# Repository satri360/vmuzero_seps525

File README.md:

# vmuzero_seps525
Dreamcast VMU powered by Raspberry Pi Zero Project

Check [Build Instructions](https://sudomod.com/forum/viewtopic.php?f=62&t=6917) in sudomod.

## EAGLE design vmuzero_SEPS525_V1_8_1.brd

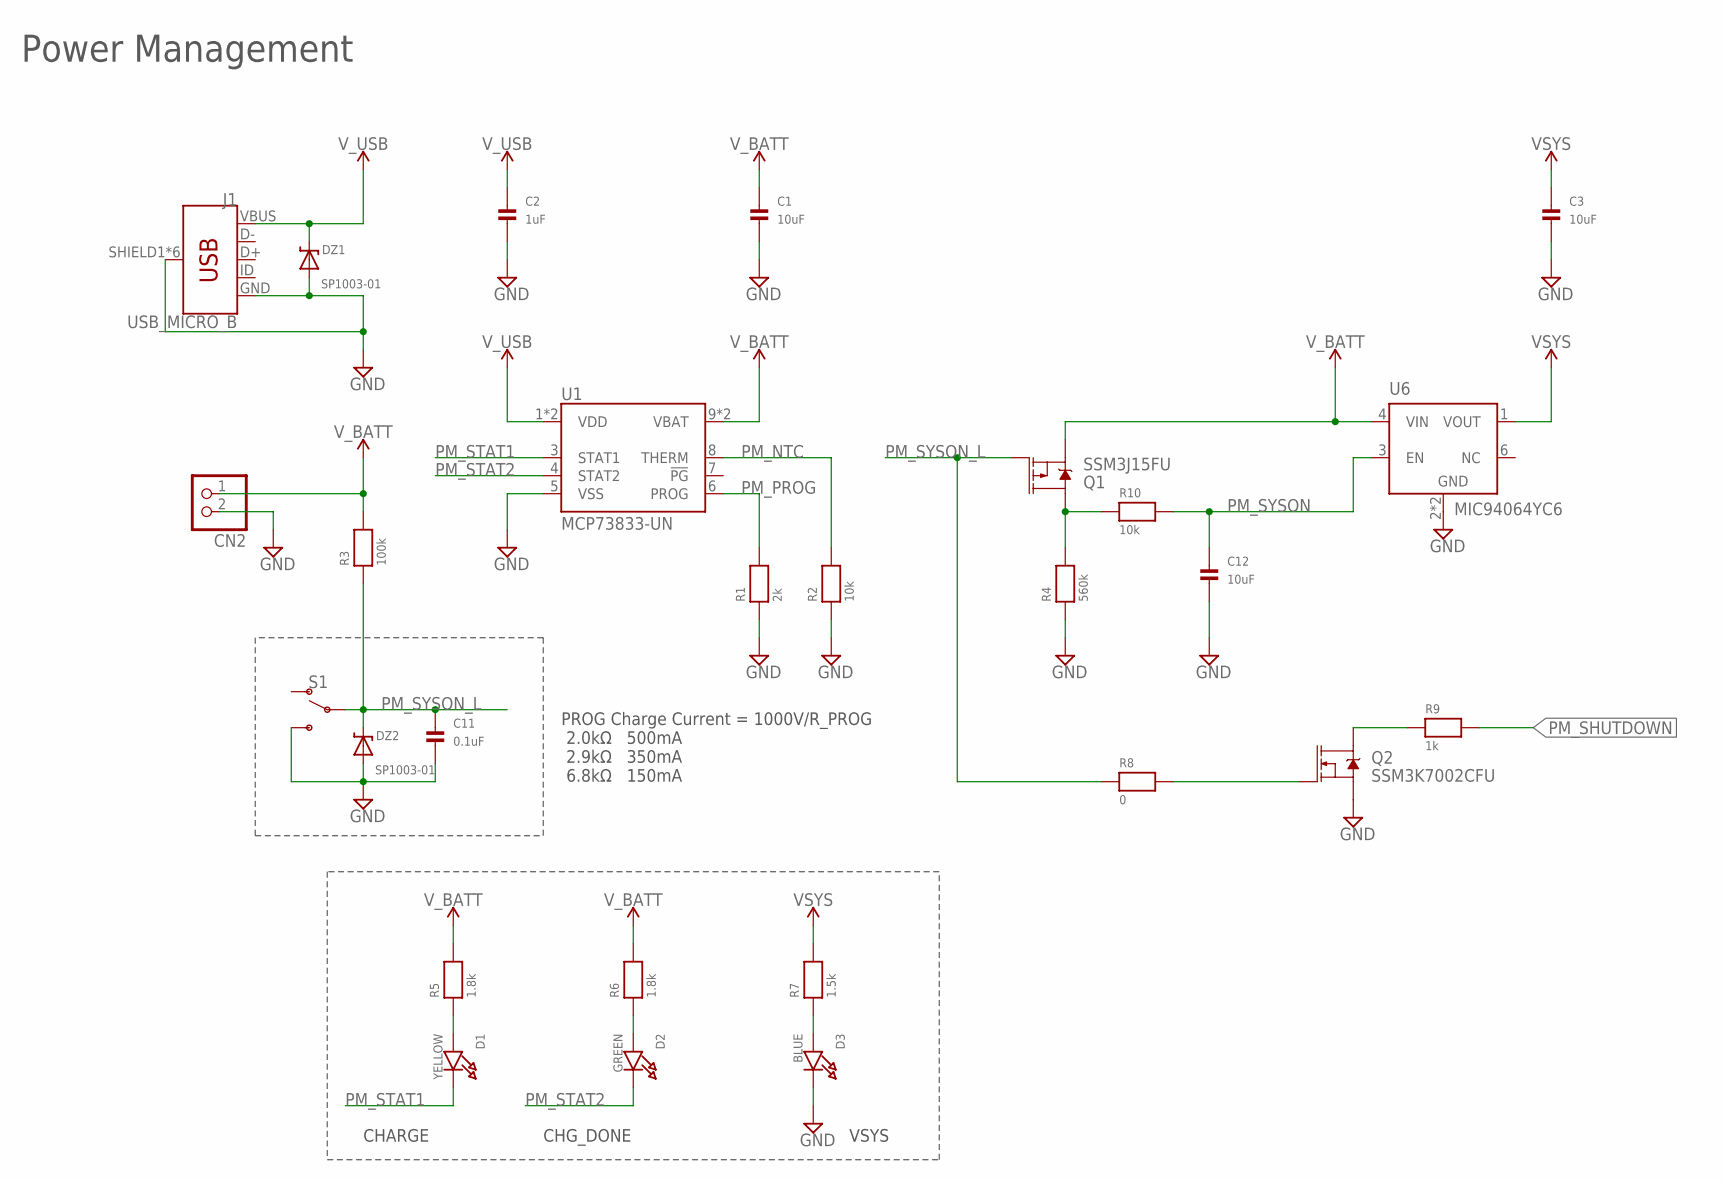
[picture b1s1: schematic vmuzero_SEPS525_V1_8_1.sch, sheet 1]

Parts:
C1, C3, C12: 10uF; _0805MP
C2: 1uF; _0805MP
C11: 0.1uF; _0805MP
CN2: JST_2PIN; S2B-PH-K-S
D1: YELLOW; CHIPLED_0805_NOOUTLINE
D2: GREEN; CHIPLED_0805_NOOUTLINE
D3: BLUE; CHIPLED_0805_NOOUTLINE
DZ1, DZ2: SP1003-01; DIODE_SOD723
J1: USB_MICRO_B; USB-MICROB_10118192
Q1: SSM3J15FU; SOT323
Q2: SSM3K7002CFU; SOT323
R1: 2k; _0805MP
R2, R10: 10k; _0805MP
R3: 100k; _0805MP
R4: 560k; _0805MP
R5, R6: 1.8k; _0805MP
R7: 1.5k; _0805MP
R8: 0; _0805MP
R9: 1k; _0805MP
S1: SWITCH-SPDT; SPDT_JS102011SAQN
U1: MCP73833-UN; 10L_MSOP
U6: MIC94064YC6; SC70-6L

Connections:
GND: C1.2, C2.2, C3.2, C11.2, C12.2, CN2.2 (1), D3.C, DZ1.A, DZ2.A, J1.GND, J1.SHIELD1 (SHIELD), J1.SHIELD2 (SHIELD), J1.SHIELD3 (SHIELD), J1.SHIELD4 (SHIELD), J1.SHIELD5 (SHIELD), J1.SHIELD6 (SHIELD), Q2.2 (S), R1.1, R2.1, R4.1, S1.P$3 (S), U1.5 (VSS), U6.2 (GND), U6.5 (GND); also elsewhere on the board
unnamed: D1.A, R5.1
unnamed: Q2.3 (D), R9.1
unnamed: D3.A, R7.1
unnamed: D2.A, R6.1
unnamed: Q2.1 (G), R8.2
unnamed: Q1.3 (D), R4.2, R10.1
PM_NTC: R2.2, U1.8 (THERM)
PM_PROG: R1.2, U1.6 (PROG)
PM_SHUTDOWN: R9.2; also elsewhere on the board
PM_STAT1: D1.C, U1.3 (STAT1)
PM_STAT2: D2.C, U1.4 (STAT2)
PM_SYSON: C12.1, R10.2, U6.3 (EN)
PM_SYSON_L: C11.1, DZ2.C, Q1.1 (G), R3.1, R8.1, S1.P$2
VSYS: C3.1, R7.2, U6.1 (VOUT); also elsewhere on the board
V_BATT: C1.1, CN2.1 (2), Q1.2 (S), R3.2, R5.2, R6.2, U1.9 (VBAT), U1.10 (VBAT), U6.4 (VIN)
V_USB: C2.1, DZ1.C, J1.VBUS, U1.1 (VDD), U1.2 (VDD)

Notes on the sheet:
Power Management
PROG Charge Current = 1000V/R_PROG 2.0kΩ 500mA 2.9kΩ 350mA 6.8kΩ 150mA
CHARGE
CHG_DONE
VSYS

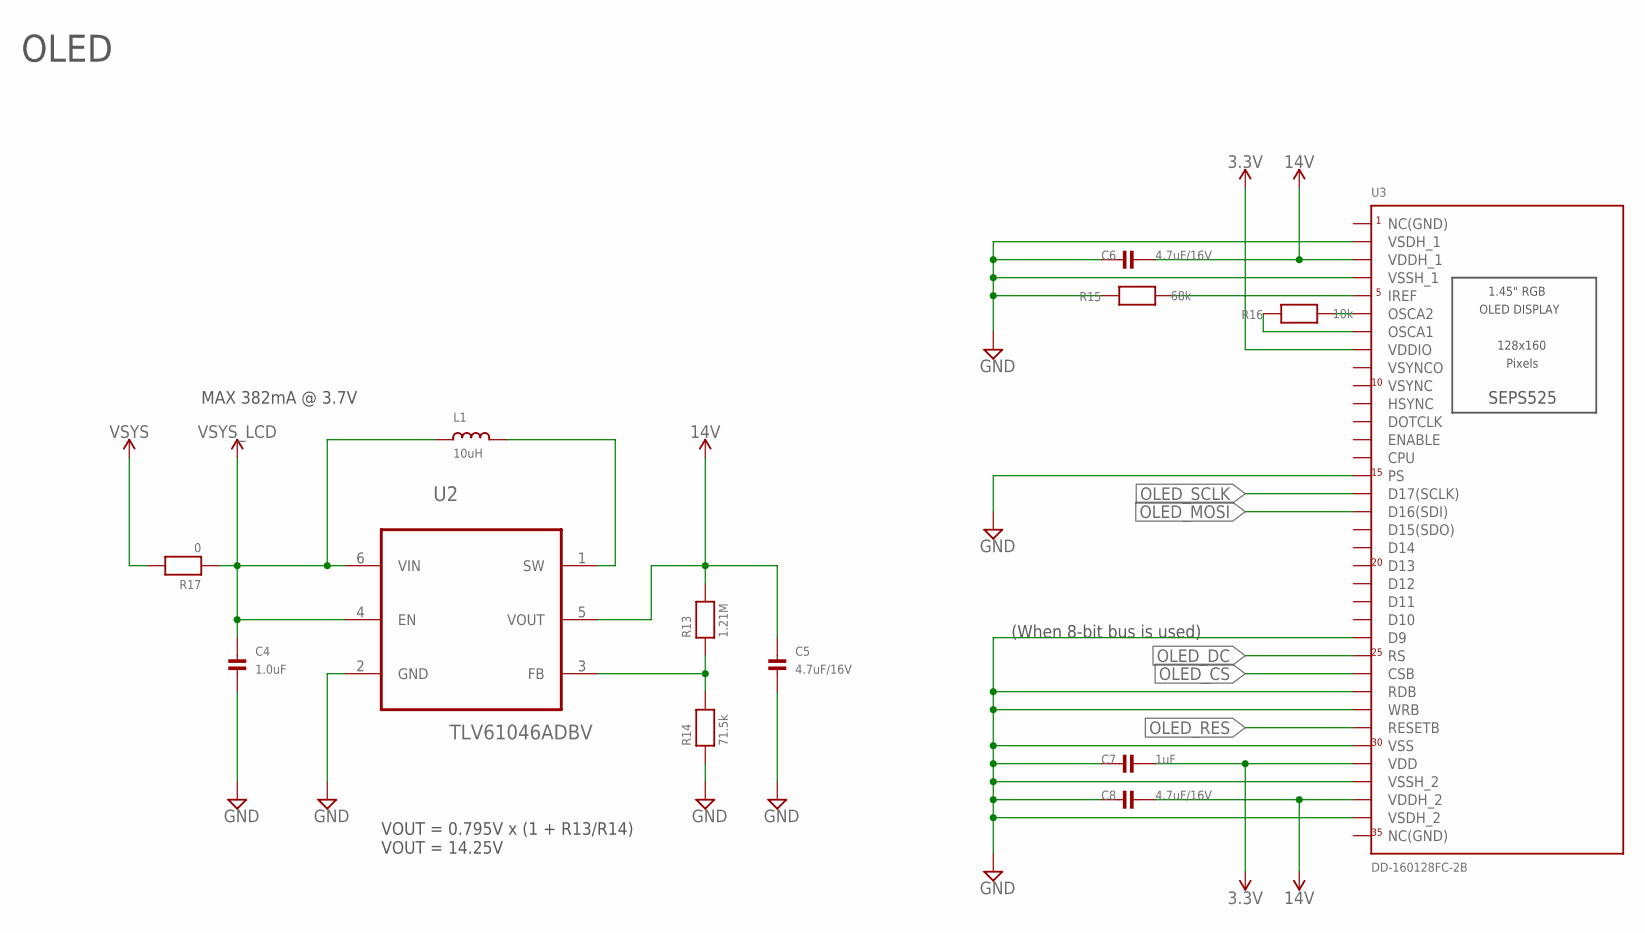
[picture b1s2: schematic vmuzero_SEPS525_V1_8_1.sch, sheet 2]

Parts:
C4: 1.0uF; _0805MP
C5, C6, C8: 4.7uF/16V; _0805MP
C7: 1uF; _0805MP
L1: 10uH; CIG22L
R13: 1.21M; _0805MP
R14: 71.5k; _0805MP
R15: 68k; _0805MP
R16: 10k; _0805MP
R17: 0; _0805MP
U2: TLV61046ADBV; R-PDSO-G6
U3: DD-160128FC-2B; XF2M-3515-1A

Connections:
3.3V: C7.1, U3.8 (VDDIO), U3.31 (VDD); also elsewhere on the board
14V: C5.1, C6.1, C8.1, R13.2, U2.5 (VOUT), U3.3 (VDDH_1), U3.33 (VDDH_2); also elsewhere on the board
GND: C4.2, C5.2, C6.2, C7.2, C8.2, R14.1, R15.2, U2.2 (GND), U3.2 (VSDH_1), U3.4 (VSSH_1), U3.15 (PS), U3.24 (D9), U3.27 (RDB), U3.28 (WRB), U3.30 (VSS), U3.32 (VSSH_2), U3.34 (VSDH_2); also elsewhere on the board
unnamed: R15.1, U3.5 (IREF)
unnamed: L1.P$2 (2), U2.1 (SW)
unnamed: R13.1, R14.2, U2.3 (FB)
unnamed: R16.1, U3.6 (OSCA2)
unnamed: R16.2, U3.7 (OSCA1)
OLED_CS: U3.26 (CSB); also elsewhere on the board
OLED_DC: U3.25 (RS); also elsewhere on the board
OLED_MOSI: U3.17 (D16(SDI)); also elsewhere on the board
OLED_RES: U3.29 (RESETB); also elsewhere on the board
OLED_SCLK: U3.16 (D17(SCLK)); also elsewhere on the board
VSYS: R17.2; also elsewhere on the board
VSYS_LCD: C4.1, L1.P$1 (1), R17.1, U2.4 (EN), U2.6 (VIN)

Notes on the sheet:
OLED
VOUT = 0.795V x (1 + R13/R14) VOUT = 14.25V
(When 8-bit bus is used)
MAX 382mA @ 3.7V

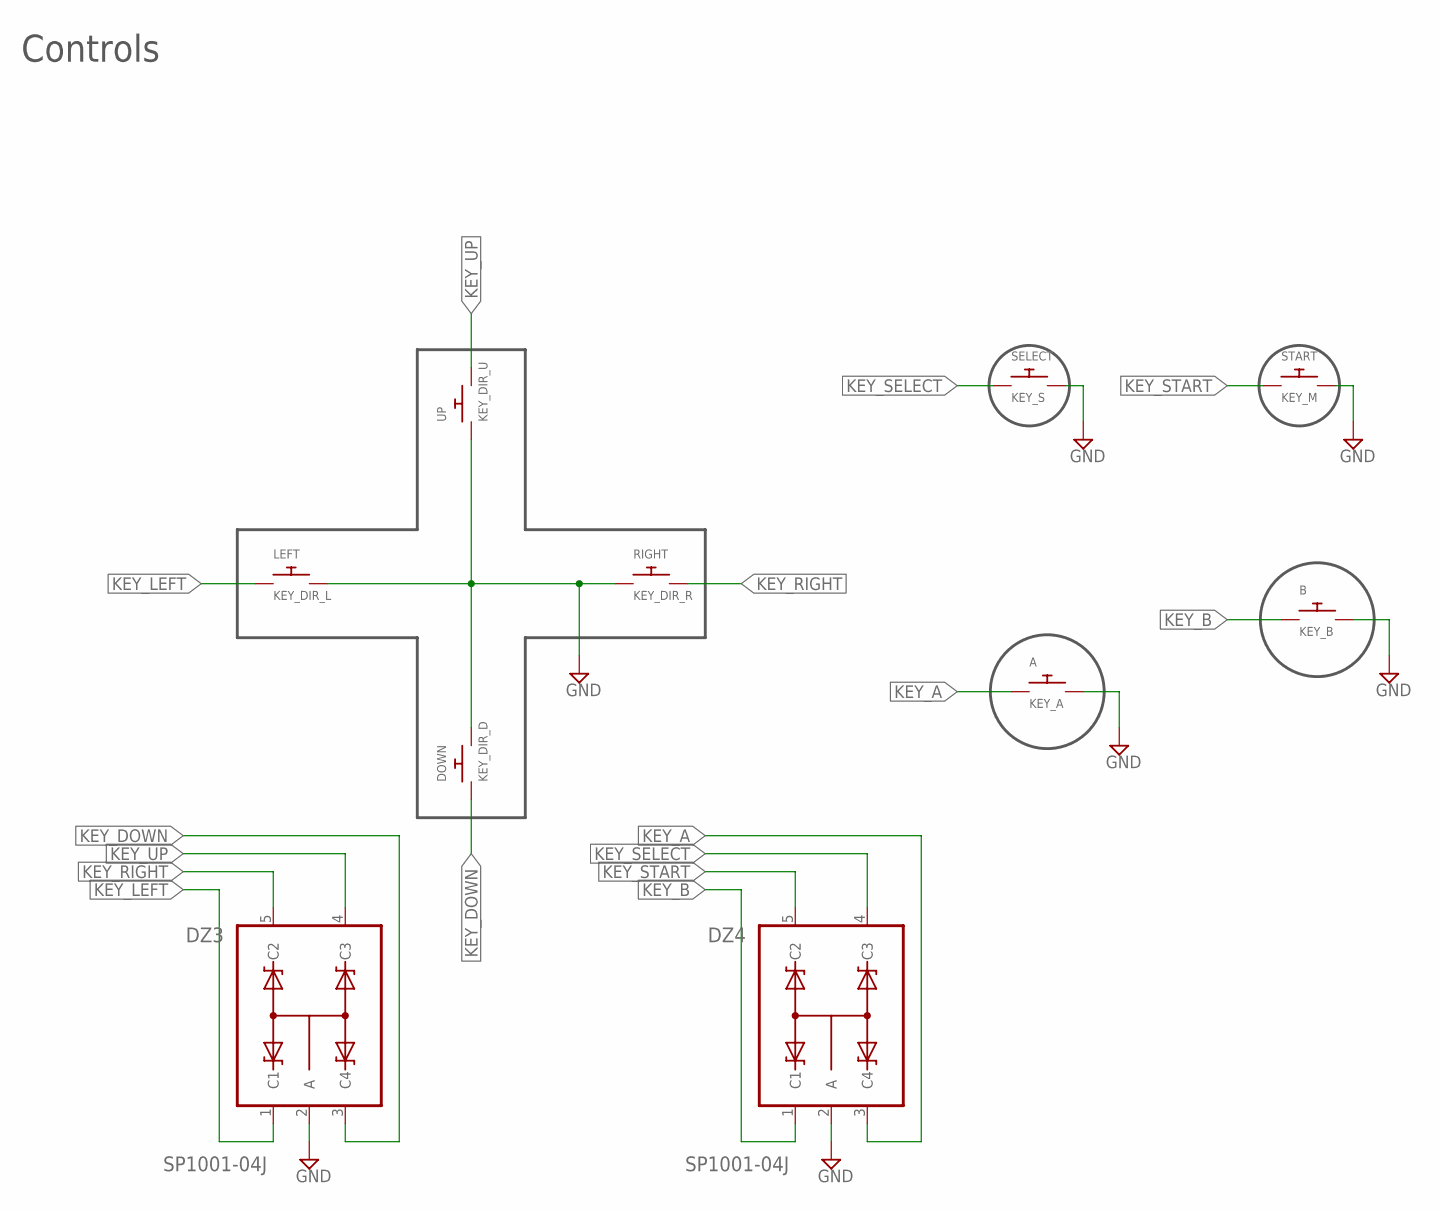
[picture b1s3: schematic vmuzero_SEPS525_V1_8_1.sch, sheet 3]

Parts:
A: KEY_A; KEYPAD_VMU_R26
B: KEY_B; KEYPAD_VMU_R26
DOWN: KEY_DIR_D; KEYPAD_VMU_R26
DZ3, DZ4: SP1001-04J; SC70-5
LEFT: KEY_DIR_L; KEYPAD_VMU_R26
RIGHT: KEY_DIR_R; KEYPAD_VMU_R26
SELECT: KEY_S; KEYPAD_VMU_R26
START: KEY_M; KEYPAD_VMU_R26
UP: KEY_DIR_U; KEYPAD_VMU_R26

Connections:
GND: A.2, B.2, DOWN.2, DZ3.2 (A), DZ4.2 (A), LEFT.2, RIGHT.1, SELECT.2, START.2, UP.1; also elsewhere on the board
KEY_A: A.1, DZ4.3 (C4); also elsewhere on the board
KEY_B: B.1, DZ4.1 (C1); also elsewhere on the board
KEY_DOWN: DOWN.1, DZ3.3 (C4); also elsewhere on the board
KEY_LEFT: DZ3.1 (C1), LEFT.1; also elsewhere on the board
KEY_RIGHT: DZ3.5 (C2), RIGHT.2; also elsewhere on the board
KEY_SELECT: DZ4.4 (C3), SELECT.1; also elsewhere on the board
KEY_START: DZ4.5 (C2), START.1; also elsewhere on the board
KEY_UP: DZ3.4 (C3), UP.2; also elsewhere on the board

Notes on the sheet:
Controls

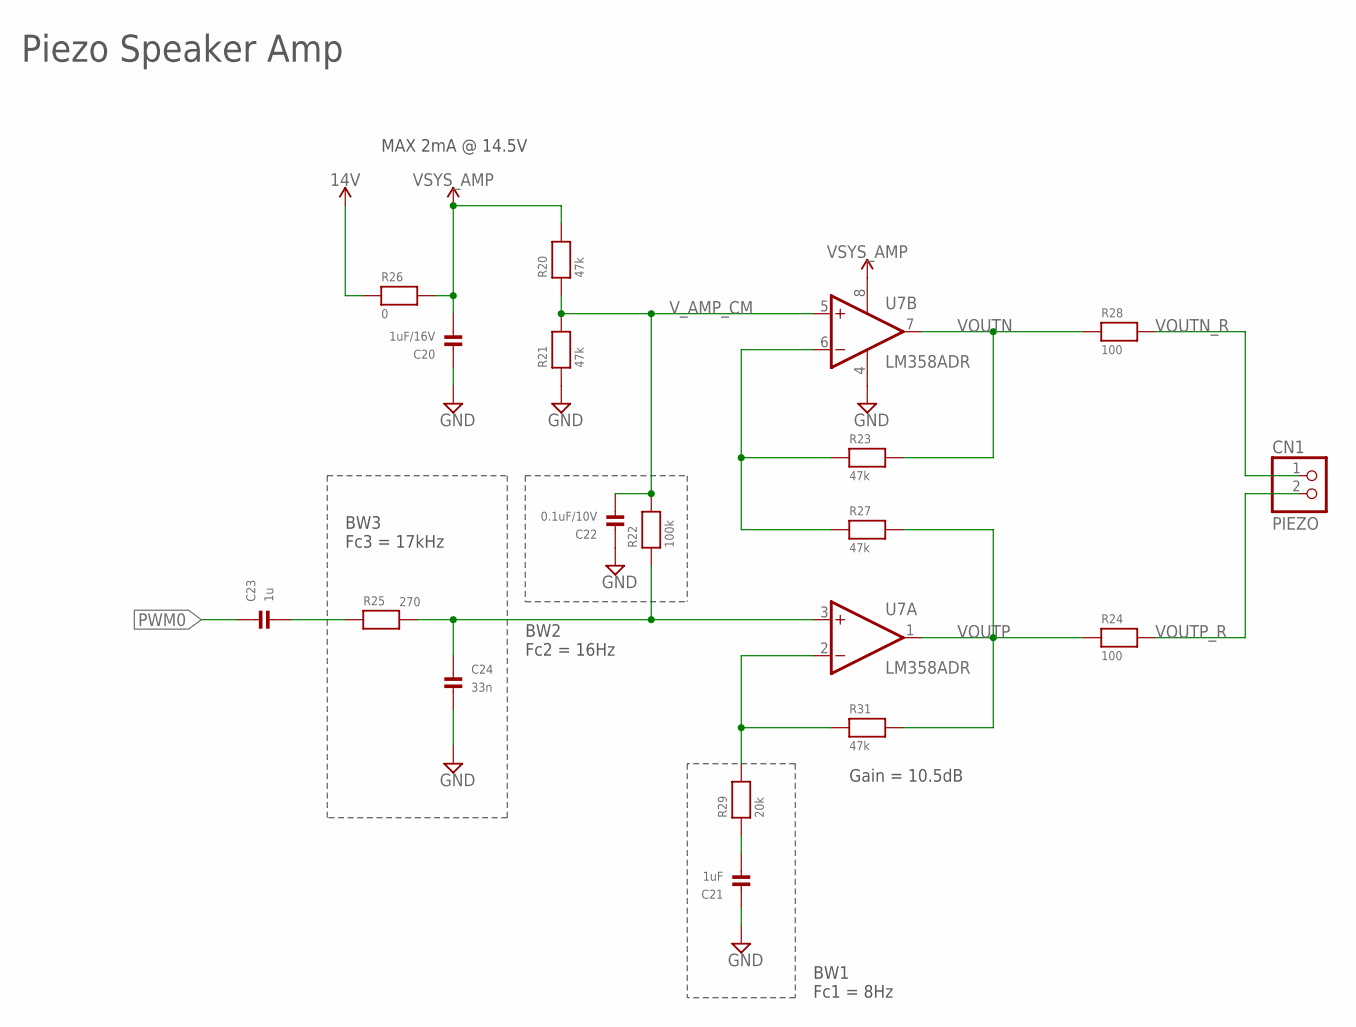
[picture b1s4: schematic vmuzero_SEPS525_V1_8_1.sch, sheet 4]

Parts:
C20: 1uF/16V; _0805MP
C21: 1uF; _0805MP
C22: 0.1uF/10V; _0805MP
C23: 1u; _0805MP
C24: 33n; _0805MP
CN1: PIEZO; 1X02_ROUND
R20, R21, R23, R27, R31: 47k; _0805MP
R22: 100k; _0805MP
R24, R28: 100; _0805MP
R25: 270; _0805MP
R26: 0; _0805MP
R29: 20k; _0805MP
U7: LM358ADR; SO08

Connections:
14V: R26.1; also elsewhere on the board
GND: C20.1, C21.1, C22.1, C24.2, R21.1, U7.4 (V-); also elsewhere on the board
unnamed: C23.2, R25.1
unnamed: R29.2, R31.1, U7.2 (-IN)
unnamed: C21.2, R29.1
unnamed: R23.1, R27.1, U7.6 (-IN)
unnamed: C24.1, R22.1, R25.2, U7.3 (+IN)
PWM0: C23.1; also elsewhere on the board
VOUTN: R23.2, R28.1, U7.7 (OUT)
VOUTN_R: CN1.1, R28.2
VOUTP: R24.1, R27.2, R31.2, U7.1 (OUT)
VOUTP_R: CN1.2, R24.2
VSYS_AMP: C20.2, R20.2, R26.2, U7.8 (V+)
V_AMP_CM: C22.2, R20.1, R21.2, R22.2, U7.5 (+IN)

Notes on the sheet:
Piezo Speaker Amp
BW3 Fc3 = 17kHz
MAX 2mA @ 14.5V
BW1 Fc1 = 8Hz
BW2 Fc2 = 16Hz
Gain = 10.5dB

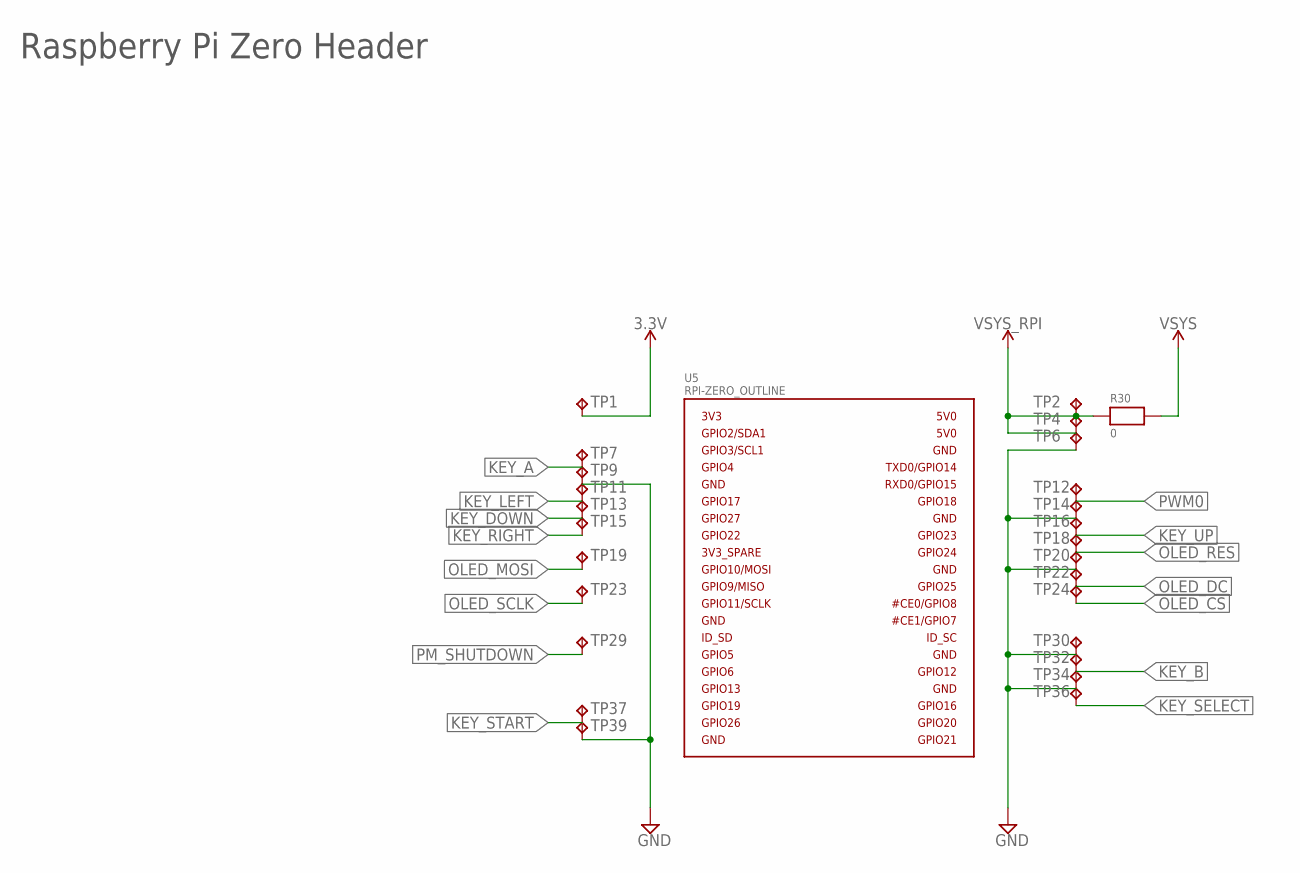
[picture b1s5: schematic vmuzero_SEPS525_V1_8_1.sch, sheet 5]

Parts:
R30: 0; _0805MP
TP1: TPTP14SQ; TP14SQ
TP2, TP4, TP6, TP7, TP9, TP11, TP12, TP13, TP14, TP15, TP16, TP18, TP19, TP20, TP22, TP23, TP24, TP29, TP30, TP32, TP34, TP36, TP37, TP39: TPTP14R; TP14R
U5: RPI-ZERO_OUTLINE; RASP_PI_ZERO_OUTLINE_SMD

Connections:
3.3V: TP1.TP; also elsewhere on the board
GND: TP6.TP, TP9.TP, TP14.TP, TP20.TP, TP30.TP, TP34.TP, TP39.TP; also elsewhere on the board
KEY_A: TP7.TP; also elsewhere on the board
KEY_B: TP32.TP; also elsewhere on the board
KEY_DOWN: TP13.TP; also elsewhere on the board
KEY_LEFT: TP11.TP; also elsewhere on the board
KEY_RIGHT: TP15.TP; also elsewhere on the board
KEY_SELECT: TP36.TP; also elsewhere on the board
KEY_START: TP37.TP; also elsewhere on the board
KEY_UP: TP16.TP; also elsewhere on the board
OLED_CS: TP24.TP; also elsewhere on the board
OLED_DC: TP22.TP; also elsewhere on the board
OLED_MOSI: TP19.TP; also elsewhere on the board
OLED_RES: TP18.TP; also elsewhere on the board
OLED_SCLK: TP23.TP; also elsewhere on the board
PM_SHUTDOWN: TP29.TP; also elsewhere on the board
PWM0: TP12.TP; also elsewhere on the board
VSYS: R30.2; also elsewhere on the board
VSYS_RPI: R30.1, TP2.TP, TP4.TP

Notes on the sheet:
Raspberry Pi Zero Header

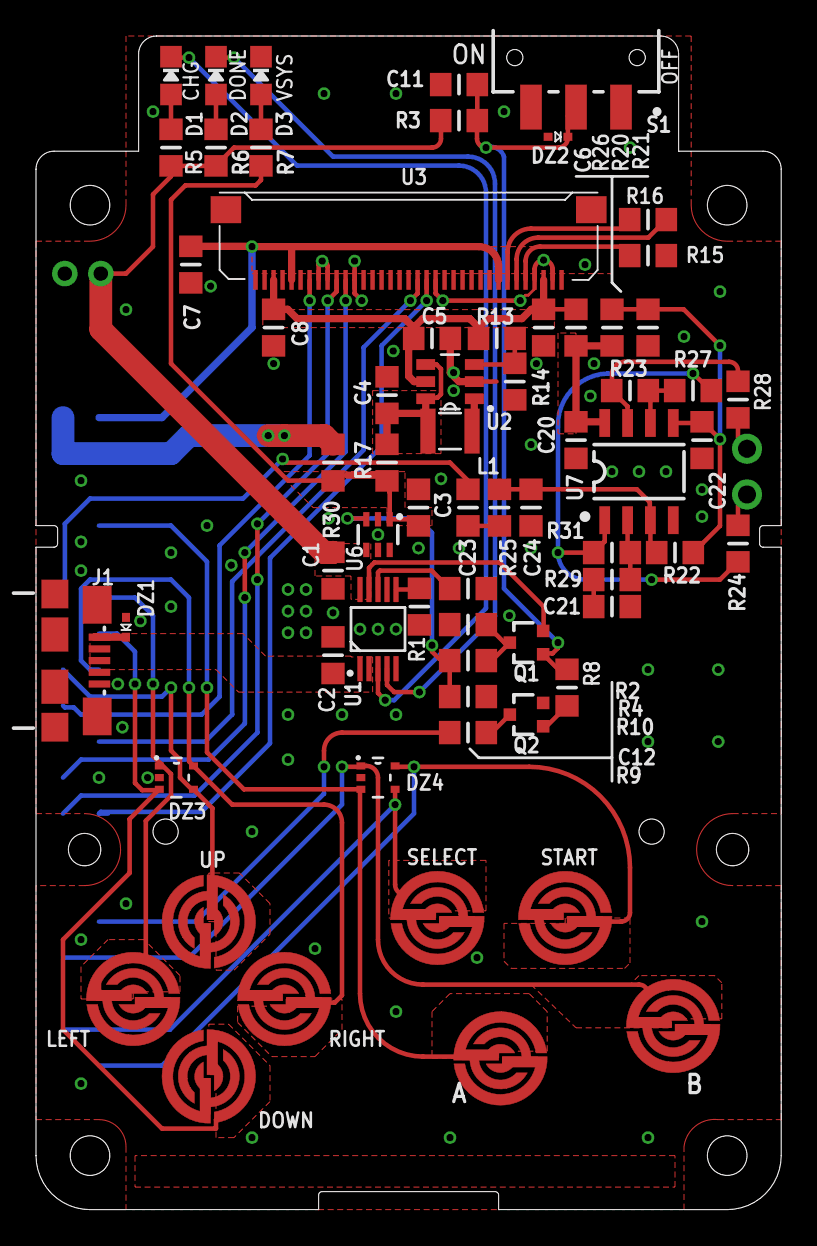
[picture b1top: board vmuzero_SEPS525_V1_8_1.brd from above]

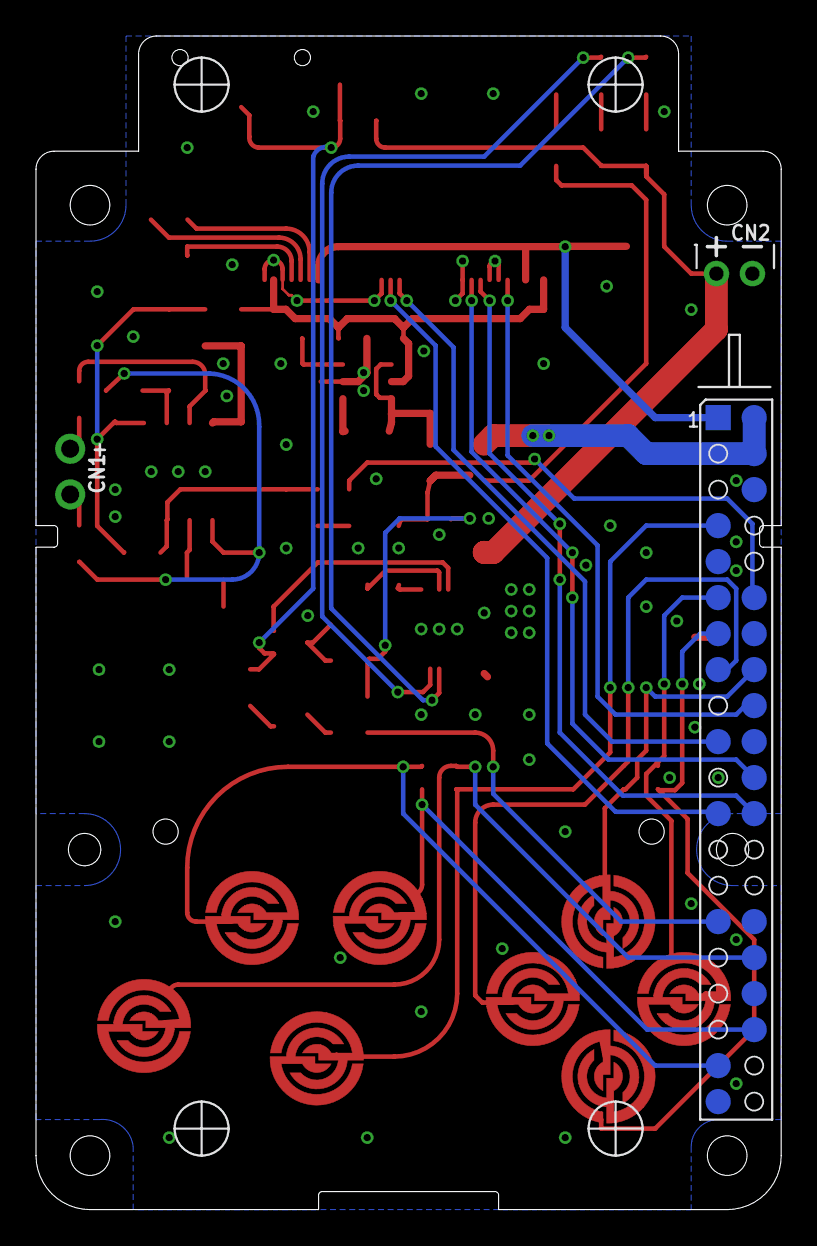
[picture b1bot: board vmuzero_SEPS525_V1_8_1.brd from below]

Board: 2 copper layers, 41.4 x 65.2 mm, 95 parts (28 on the bottom side), 51 nets.

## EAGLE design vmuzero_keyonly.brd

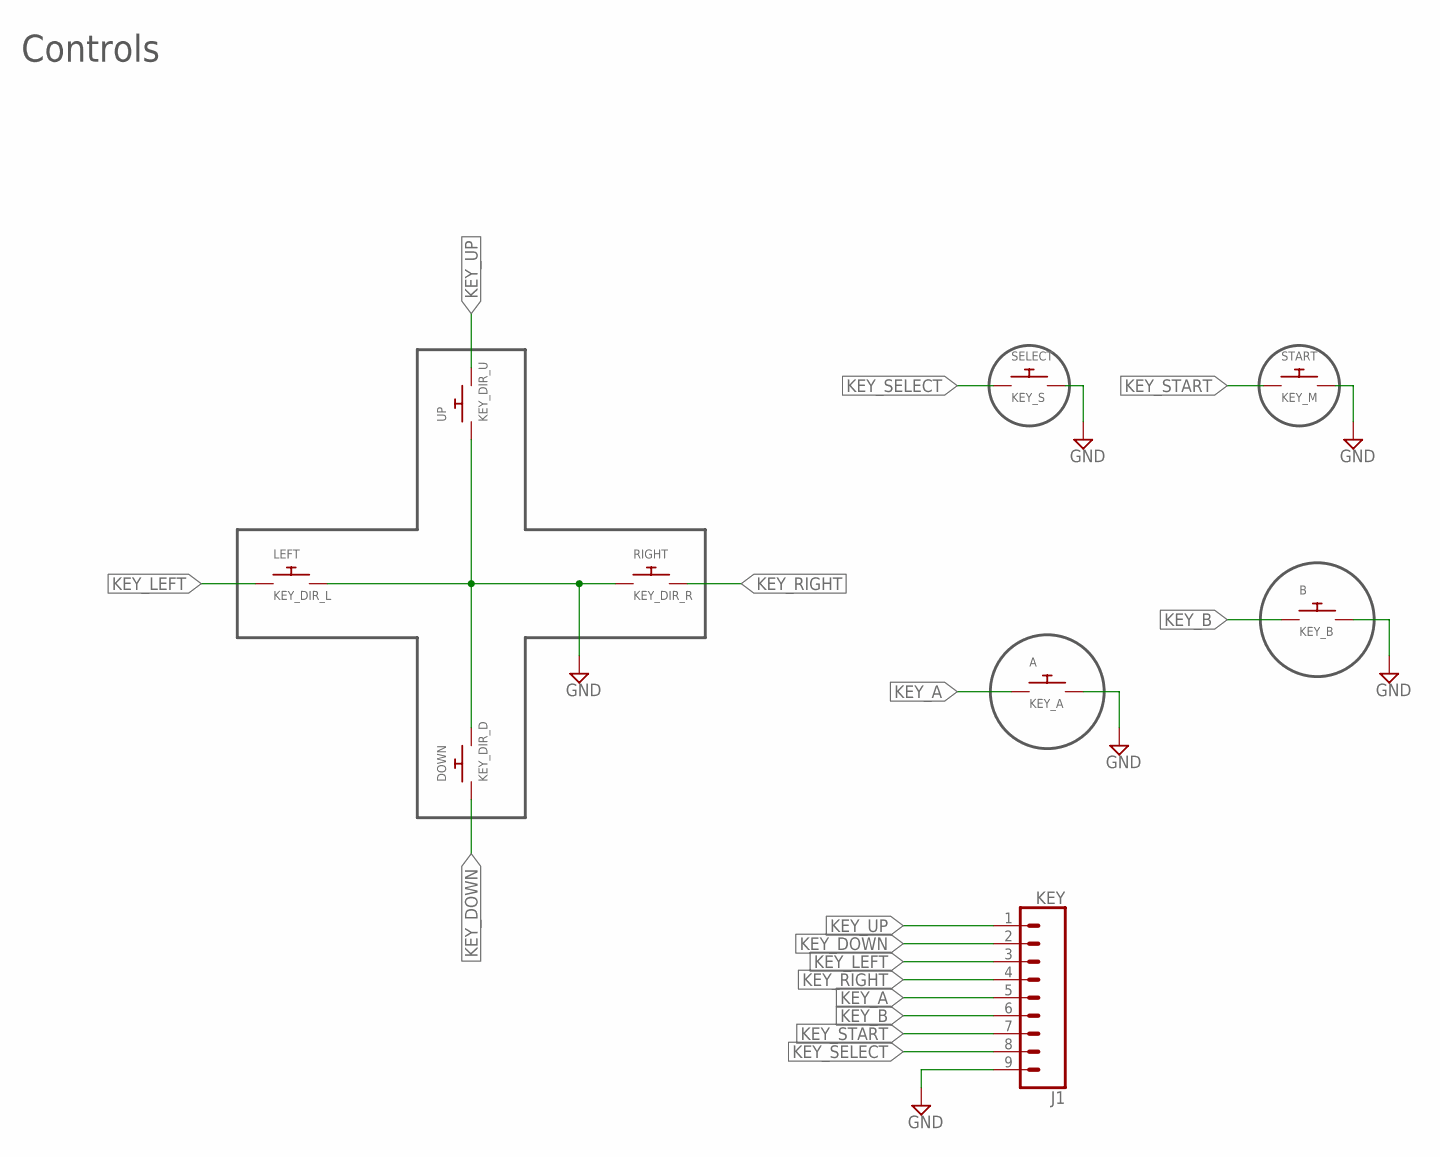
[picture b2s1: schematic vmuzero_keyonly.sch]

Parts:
A: KEY_A; KEYPAD_VMU_R26
B: KEY_B; KEYPAD_VMU_R26
DOWN: KEY_DIR_D; KEYPAD_VMU_R26
J1: KEY; 1X09_NO_SILK
LEFT: KEY_DIR_L; KEYPAD_VMU_R26
RIGHT: KEY_DIR_R; KEYPAD_VMU_R26
SELECT: KEY_S; KEYPAD_VMU_R26
START: KEY_M; KEYPAD_VMU_R26
UP: KEY_DIR_U; KEYPAD_VMU_R26

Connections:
GND: A.2, B.2, DOWN.2, J1.9, LEFT.2, RIGHT.1, SELECT.2, START.2, UP.1
KEY_A: A.1, J1.5
KEY_B: B.1, J1.6
KEY_DOWN: DOWN.1, J1.2
KEY_LEFT: J1.3, LEFT.1
KEY_RIGHT: J1.4, RIGHT.2
KEY_SELECT: J1.8, SELECT.1
KEY_START: J1.7, START.1
KEY_UP: J1.1, UP.2

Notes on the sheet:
Controls

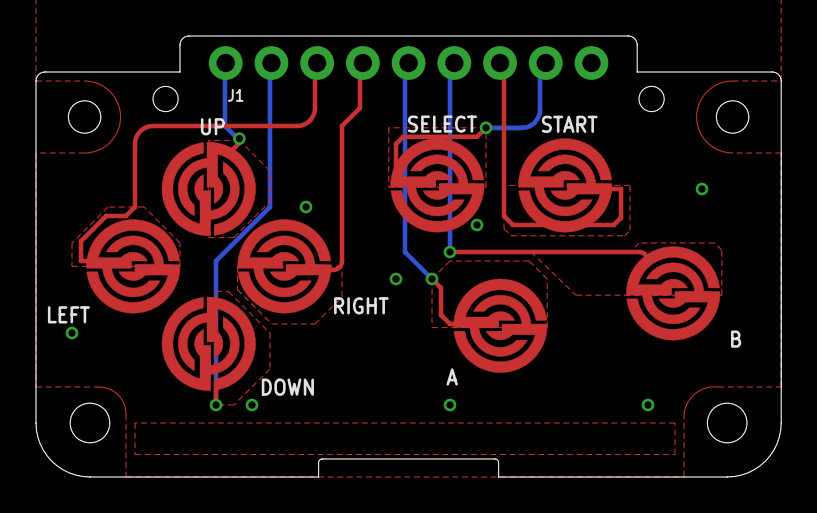
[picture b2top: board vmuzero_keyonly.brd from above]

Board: 2 copper layers, 41.4 x 24.5 mm, 9 parts (0 on the bottom side), 9 nets.

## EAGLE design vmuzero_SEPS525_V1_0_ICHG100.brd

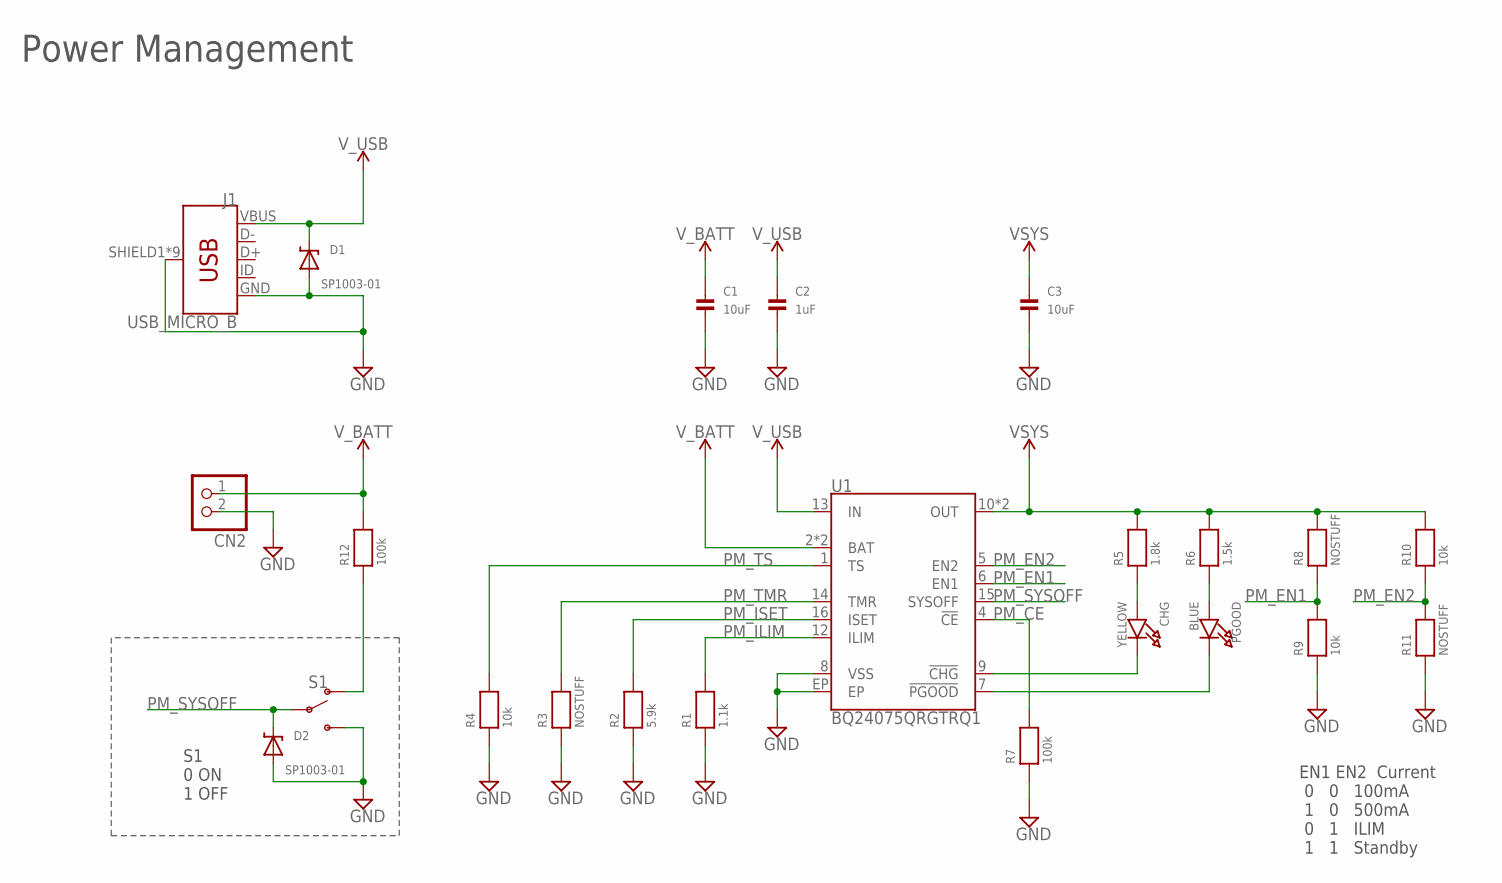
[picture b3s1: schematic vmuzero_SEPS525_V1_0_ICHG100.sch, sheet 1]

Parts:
C1, C3: 10uF; _0805MP
C2: 1uF; _0805MP
CHG: YELLOW; CHIPLED_0805_NOOUTLINE
CN2: JST_2PIN; S2B-PH-K-S
D1, D2: SP1003-01; DIODE_SOD723
J1: USB_MICRO_B; UJ2-MIBH2-4-SMT
PGOOD: BLUE; CHIPLED_0805_NOOUTLINE
R1: 1.1k; _0805MP
R2: 5.9k; _0805MP
R3, R8, R11: NOSTUFF; _0805MP
R4, R9, R10: 10k; _0805MP
R5: 1.8k; _0805MP
R6: 1.5k; _0805MP
R7, R12: 100k; _0805MP
S1: SWITCH-SPDT; SPDT_JS102011SAQN
U1: BQ24075QRGTRQ1; PVQFN-N16

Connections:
GND: C1.2, C2.2, C3.2, CN2.2 (1), D1.A, D2.A, J1.GND, J1.SHIELD1 (SHIELD), J1.SHIELD2 (SHIELD), J1.SHIELD3 (SHIELD), J1.SHIELD5 (SHIELD), J1.SHIELD6 (SHIELD), J1.SHIELD7 (SHIELD), J1.SHIELD8 (SHIELD), J1.SHIELD9 (SHIELD), J1.SHIELD10 (SHIELD), R1.1, R2.1, R3.1, R4.1, R7.1, R9.1, R11.1, S1.P$3 (S), U1.8 (VSS), U1.EP; also elsewhere on the board
unnamed: CHG.C, U1.9 (!CHG!)
unnamed: PGOOD.C, U1.7 (!PGOOD!)
unnamed: R12.1, S1.P$1 (O)
unnamed: PGOOD.A, R6.1
unnamed: CHG.A, R5.1
PM_CE: R7.2, U1.4 (!CE!)
PM_EN1: R8.1, R9.2, U1.6 (EN1)
PM_EN2: R10.1, R11.2, U1.5 (EN2)
PM_ILIM: R1.2, U1.12 (ILIM)
PM_ISET: R2.2, U1.16 (ISET)
PM_SYSOFF: D2.C, S1.P$2, U1.15 (SYSOFF)
PM_TMR: R3.2, U1.14 (TMR)
PM_TS: R4.2, U1.1 (TS)
VSYS: C3.1, R5.2, R6.2, R8.2, R10.2, U1.10 (OUT), U1.11 (OUT); also elsewhere on the board
V_BATT: C1.1, CN2.1 (2), R12.2, U1.2 (BAT), U1.3 (BAT)
V_USB: C2.1, D1.C, J1.VBUS, U1.13 (IN)

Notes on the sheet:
Power Management
EN1 EN2 Current 0 0 100mA 1 0 500mA 0 1 ILIM 1 1 Standby
S1 0 ON 1 OFF

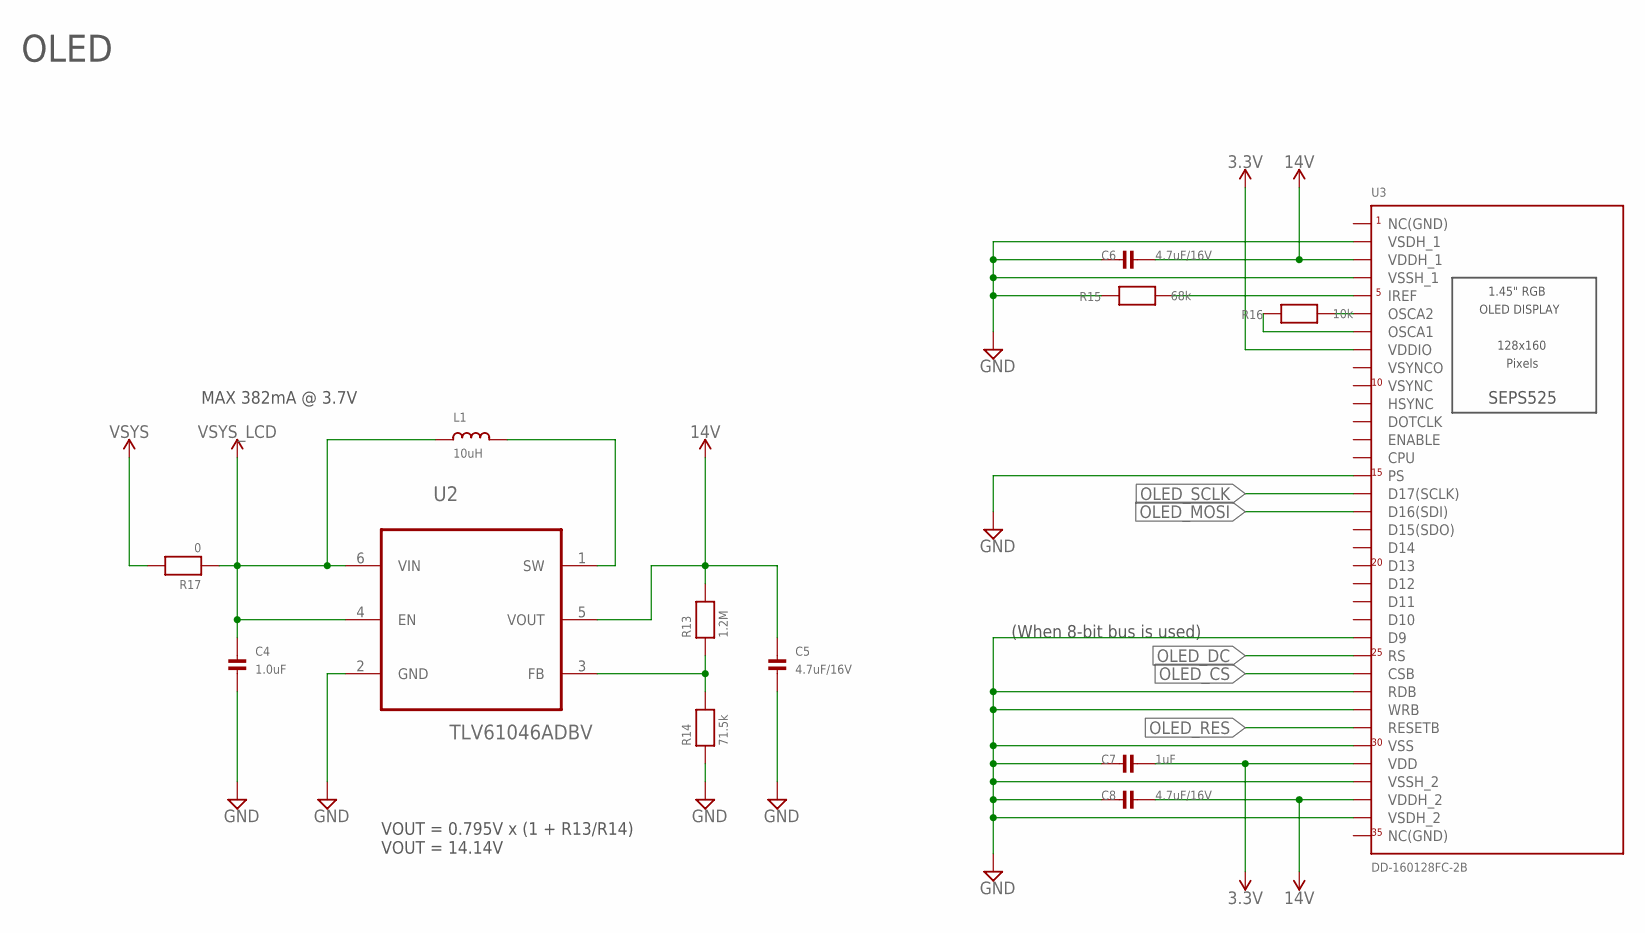
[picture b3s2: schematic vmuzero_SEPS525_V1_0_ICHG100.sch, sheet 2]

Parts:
C4: 1.0uF; _0805MP
C5, C6, C8: 4.7uF/16V; _0805MP
C7: 1uF; _0805MP
L1: 10uH; LQH2
R13: 1.2M; _0805MP
R14: 71.5k; _0805MP
R15: 68k; _0805MP
R16: 10k; _0805MP
R17: 0; _0805MP
U2: TLV61046ADBV; R-PDSO-G6
U3: DD-160128FC-2B; XF2M-3515-1A

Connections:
3.3V: C7.1, U3.8 (VDDIO), U3.31 (VDD); also elsewhere on the board
14V: C5.1, C6.1, C8.1, R13.2, U2.5 (VOUT), U3.3 (VDDH_1), U3.33 (VDDH_2)
GND: C4.2, C5.2, C6.2, C7.2, C8.2, R14.1, R15.2, U2.2 (GND), U3.2 (VSDH_1), U3.4 (VSSH_1), U3.15 (PS), U3.24 (D9), U3.27 (RDB), U3.28 (WRB), U3.30 (VSS), U3.32 (VSSH_2), U3.34 (VSDH_2); also elsewhere on the board
unnamed: R15.1, U3.5 (IREF)
unnamed: L1.P$2 (2), U2.1 (SW)
unnamed: R13.1, R14.2, U2.3 (FB)
unnamed: R16.1, U3.6 (OSCA2)
unnamed: R16.2, U3.7 (OSCA1)
OLED_CS: U3.26 (CSB); also elsewhere on the board
OLED_DC: U3.25 (RS); also elsewhere on the board
OLED_MOSI: U3.17 (D16(SDI)); also elsewhere on the board
OLED_RES: U3.29 (RESETB); also elsewhere on the board
OLED_SCLK: U3.16 (D17(SCLK)); also elsewhere on the board
VSYS: R17.2; also elsewhere on the board
VSYS_LCD: C4.1, L1.P$1 (1), R17.1, U2.4 (EN), U2.6 (VIN)

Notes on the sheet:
OLED
VOUT = 0.795V x (1 + R13/R14) VOUT = 14.14V
(When 8-bit bus is used)
MAX 382mA @ 3.7V

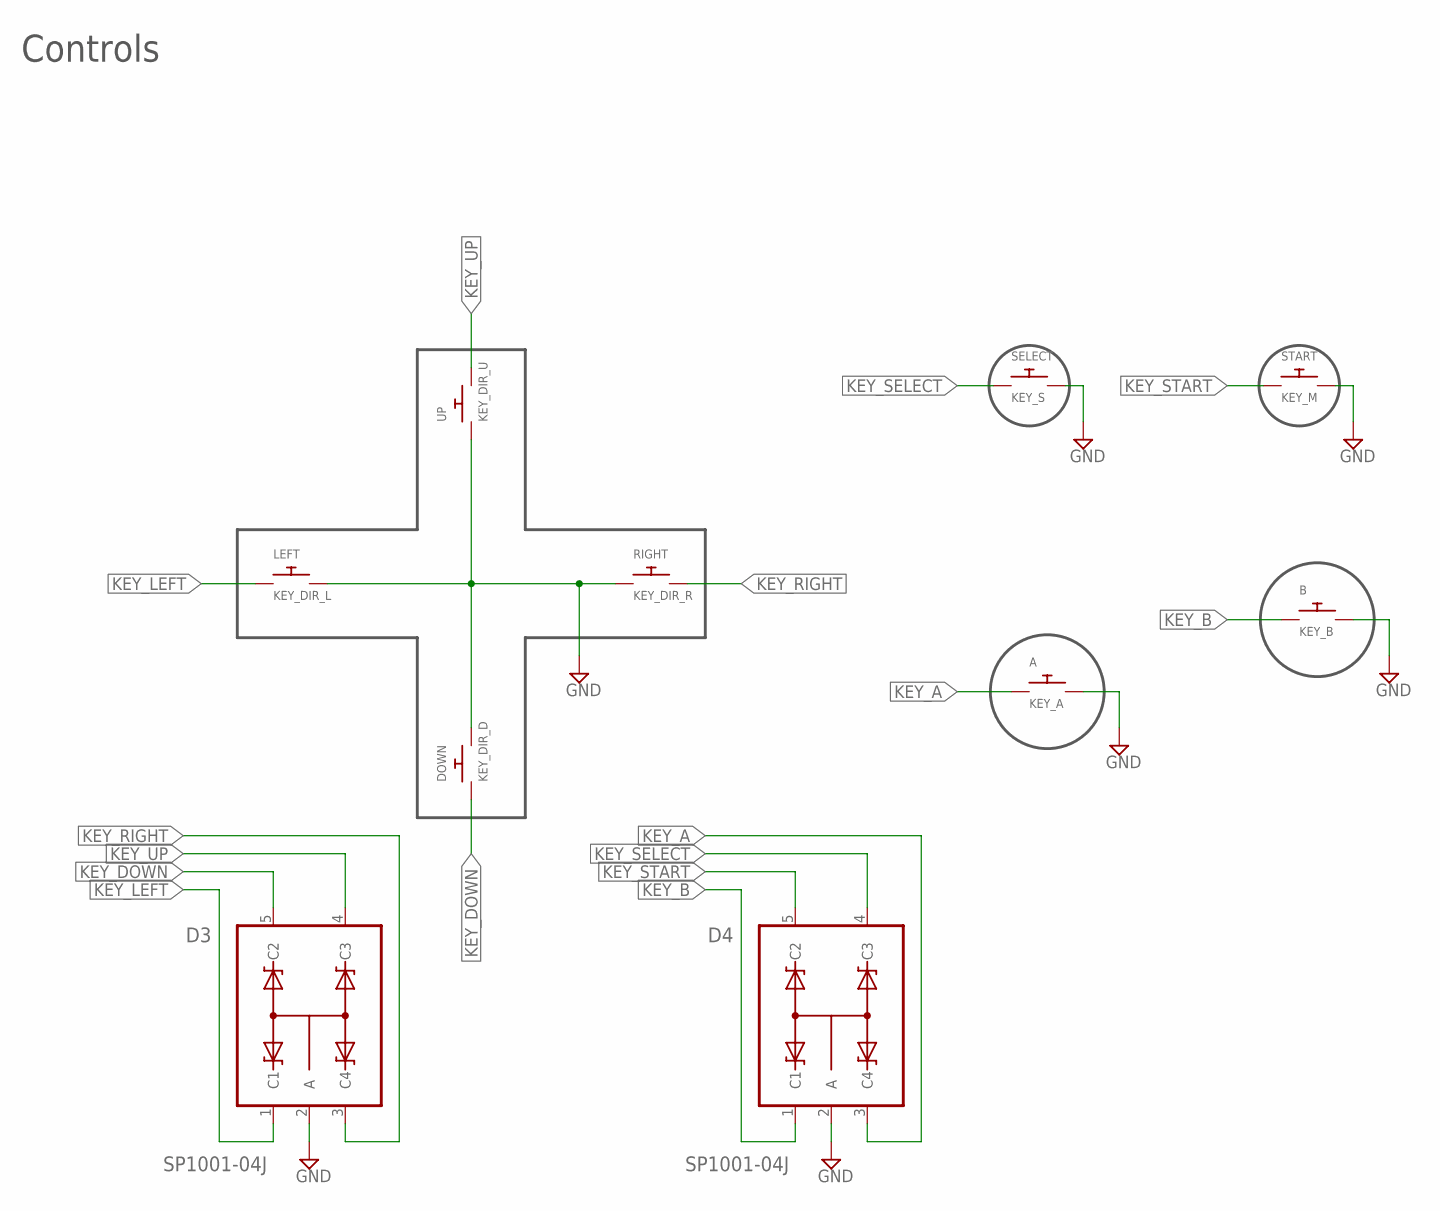
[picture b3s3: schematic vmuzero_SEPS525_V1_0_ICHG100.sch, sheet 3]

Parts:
A: KEY_A; KEYPAD_VMU_R26
B: KEY_B; KEYPAD_VMU_R26
D3, D4: SP1001-04J; SC70-5
DOWN: KEY_DIR_D; KEYPAD_VMU_R26
LEFT: KEY_DIR_L; KEYPAD_VMU_R26
RIGHT: KEY_DIR_R; KEYPAD_VMU_R26
SELECT: KEY_S; KEYPAD_VMU_R26
START: KEY_M; KEYPAD_VMU_R26
UP: KEY_DIR_U; KEYPAD_VMU_R26

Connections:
GND: A.2, B.2, D3.2 (A), D4.2 (A), DOWN.2, LEFT.2, RIGHT.1, SELECT.2, START.2, UP.1; also elsewhere on the board
KEY_A: A.1, D4.3 (C4); also elsewhere on the board
KEY_B: B.1, D4.1 (C1); also elsewhere on the board
KEY_DOWN: D3.5 (C2), DOWN.1; also elsewhere on the board
KEY_LEFT: D3.1 (C1), LEFT.1; also elsewhere on the board
KEY_RIGHT: D3.3 (C4), RIGHT.2; also elsewhere on the board
KEY_SELECT: D4.4 (C3), SELECT.1; also elsewhere on the board
KEY_START: D4.5 (C2), START.1; also elsewhere on the board
KEY_UP: D3.4 (C3), UP.2; also elsewhere on the board

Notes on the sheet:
Controls

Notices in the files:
parts and their libraries:
SparkFun-IC-Power: Licensing: Creative Commons ShareAlike 4.0 International - https://creativecommons.org/licenses/by-sa/4.0
microbuilder: This work is placed in the public domain, and may be freely used for commercial and non-commercial work with the following conditions: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
